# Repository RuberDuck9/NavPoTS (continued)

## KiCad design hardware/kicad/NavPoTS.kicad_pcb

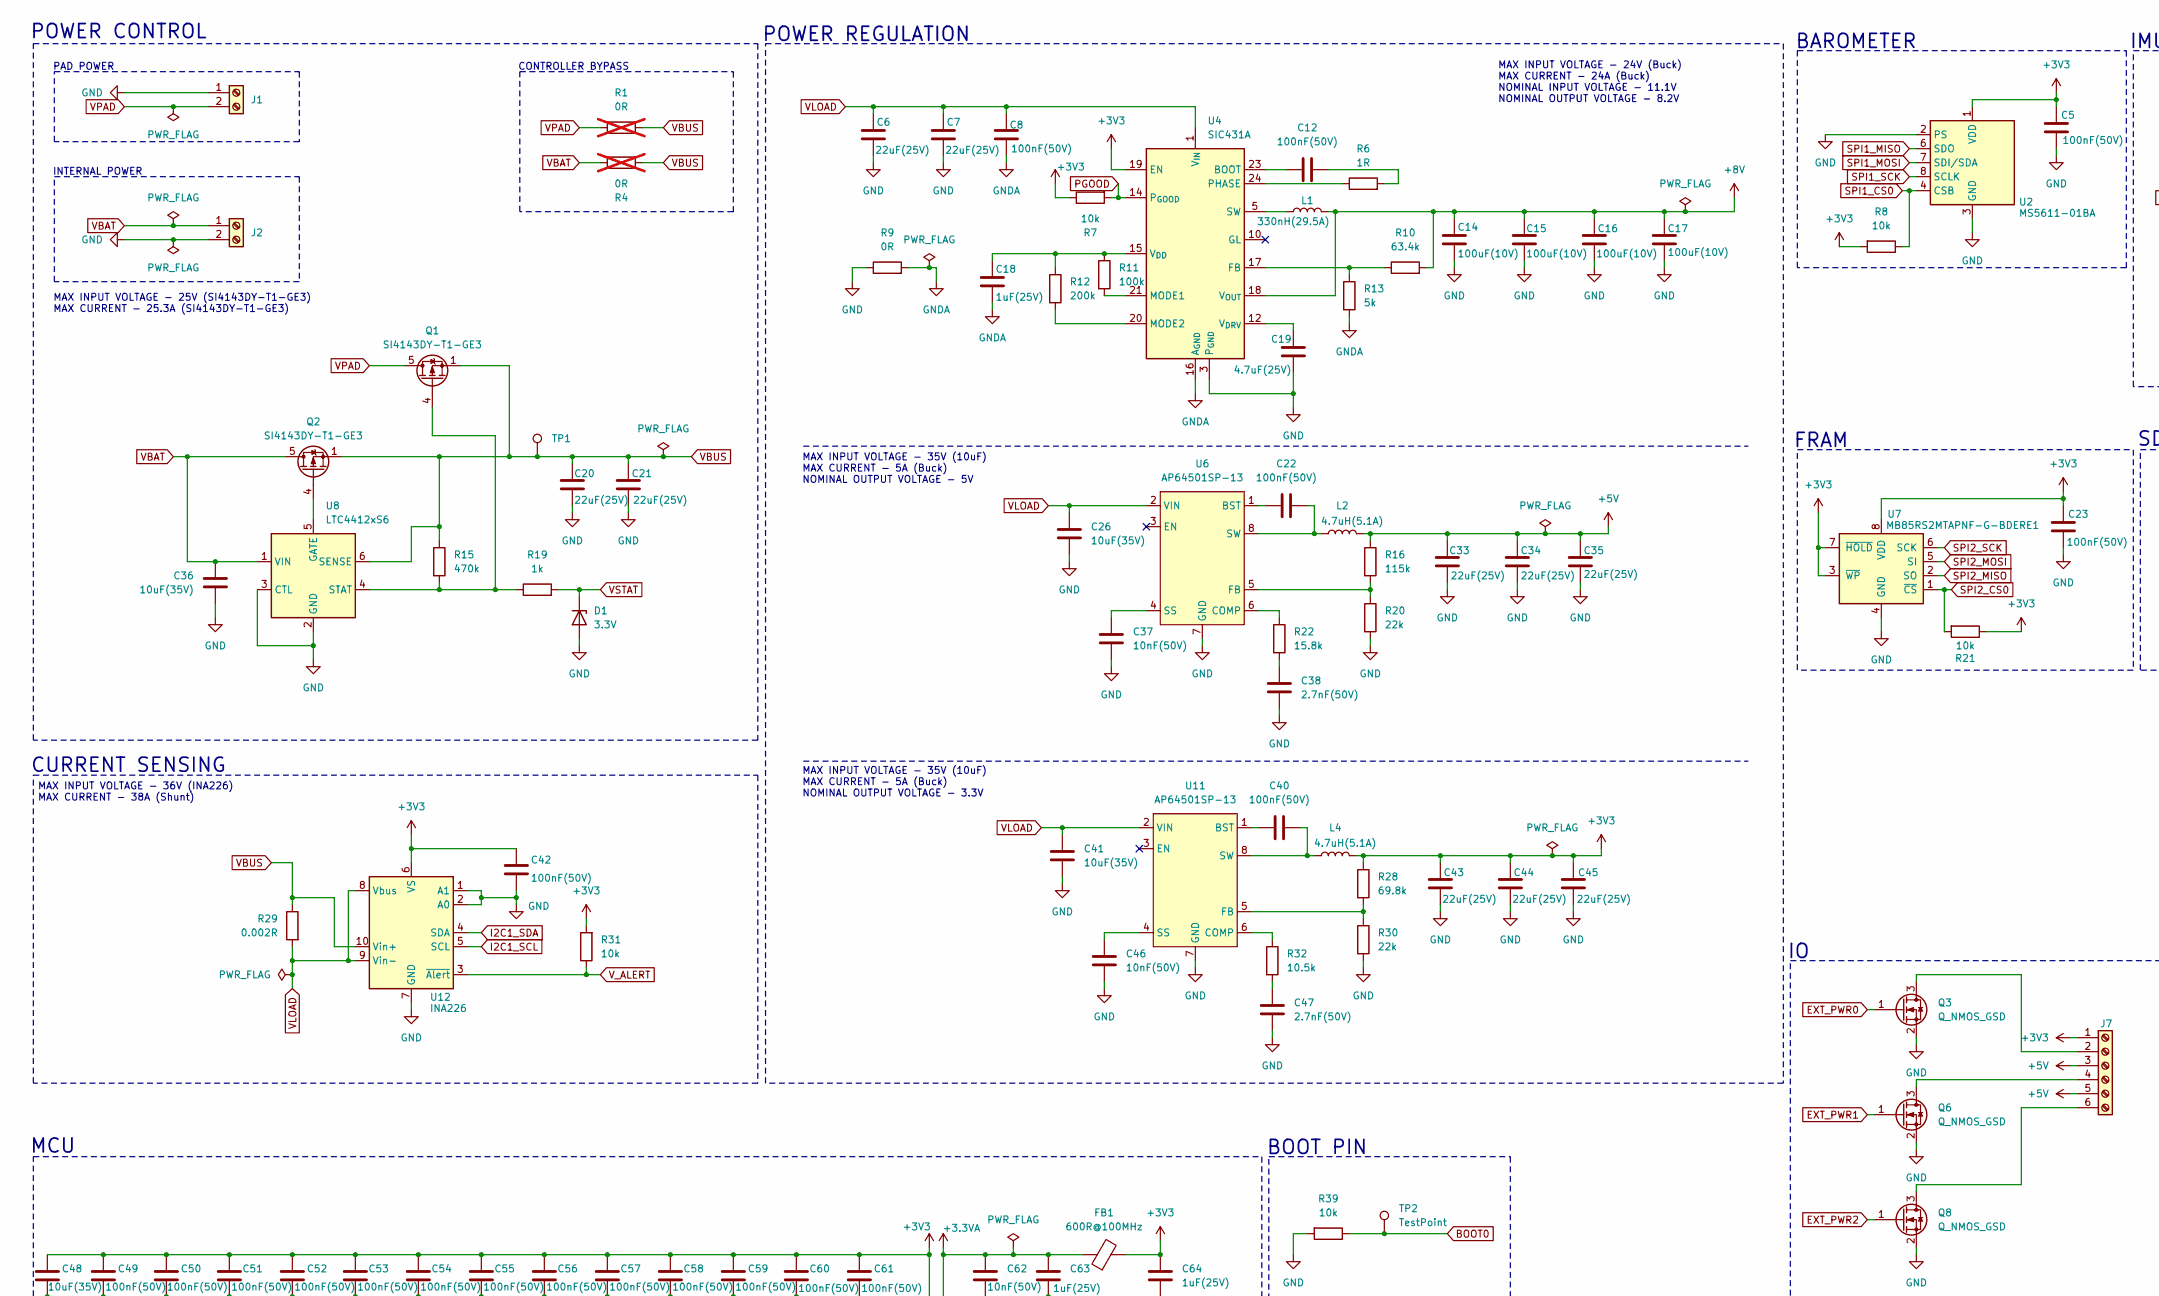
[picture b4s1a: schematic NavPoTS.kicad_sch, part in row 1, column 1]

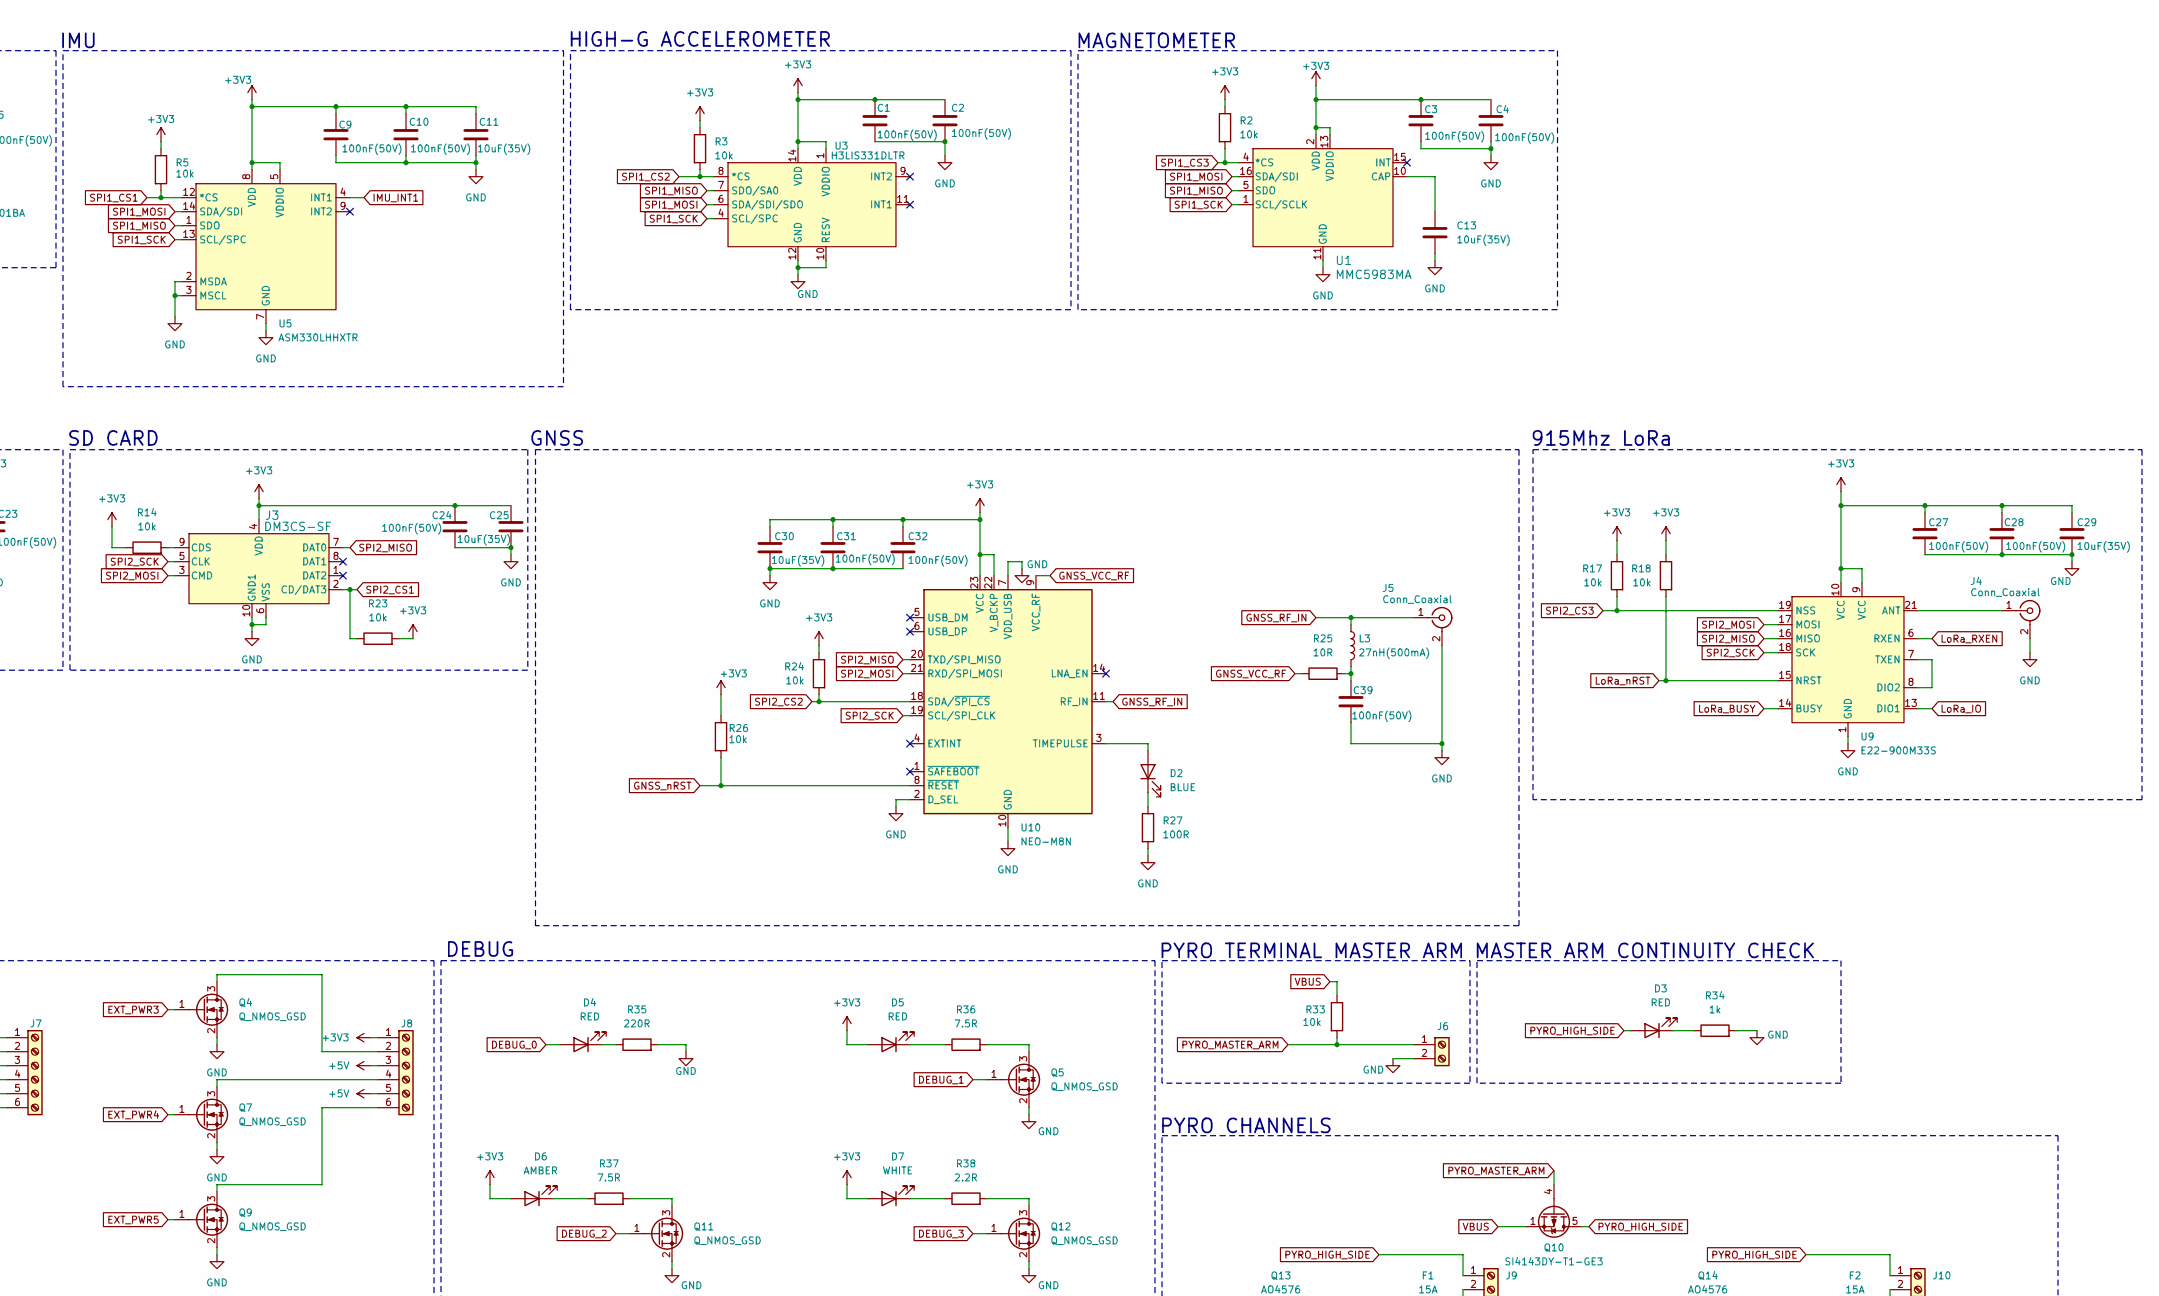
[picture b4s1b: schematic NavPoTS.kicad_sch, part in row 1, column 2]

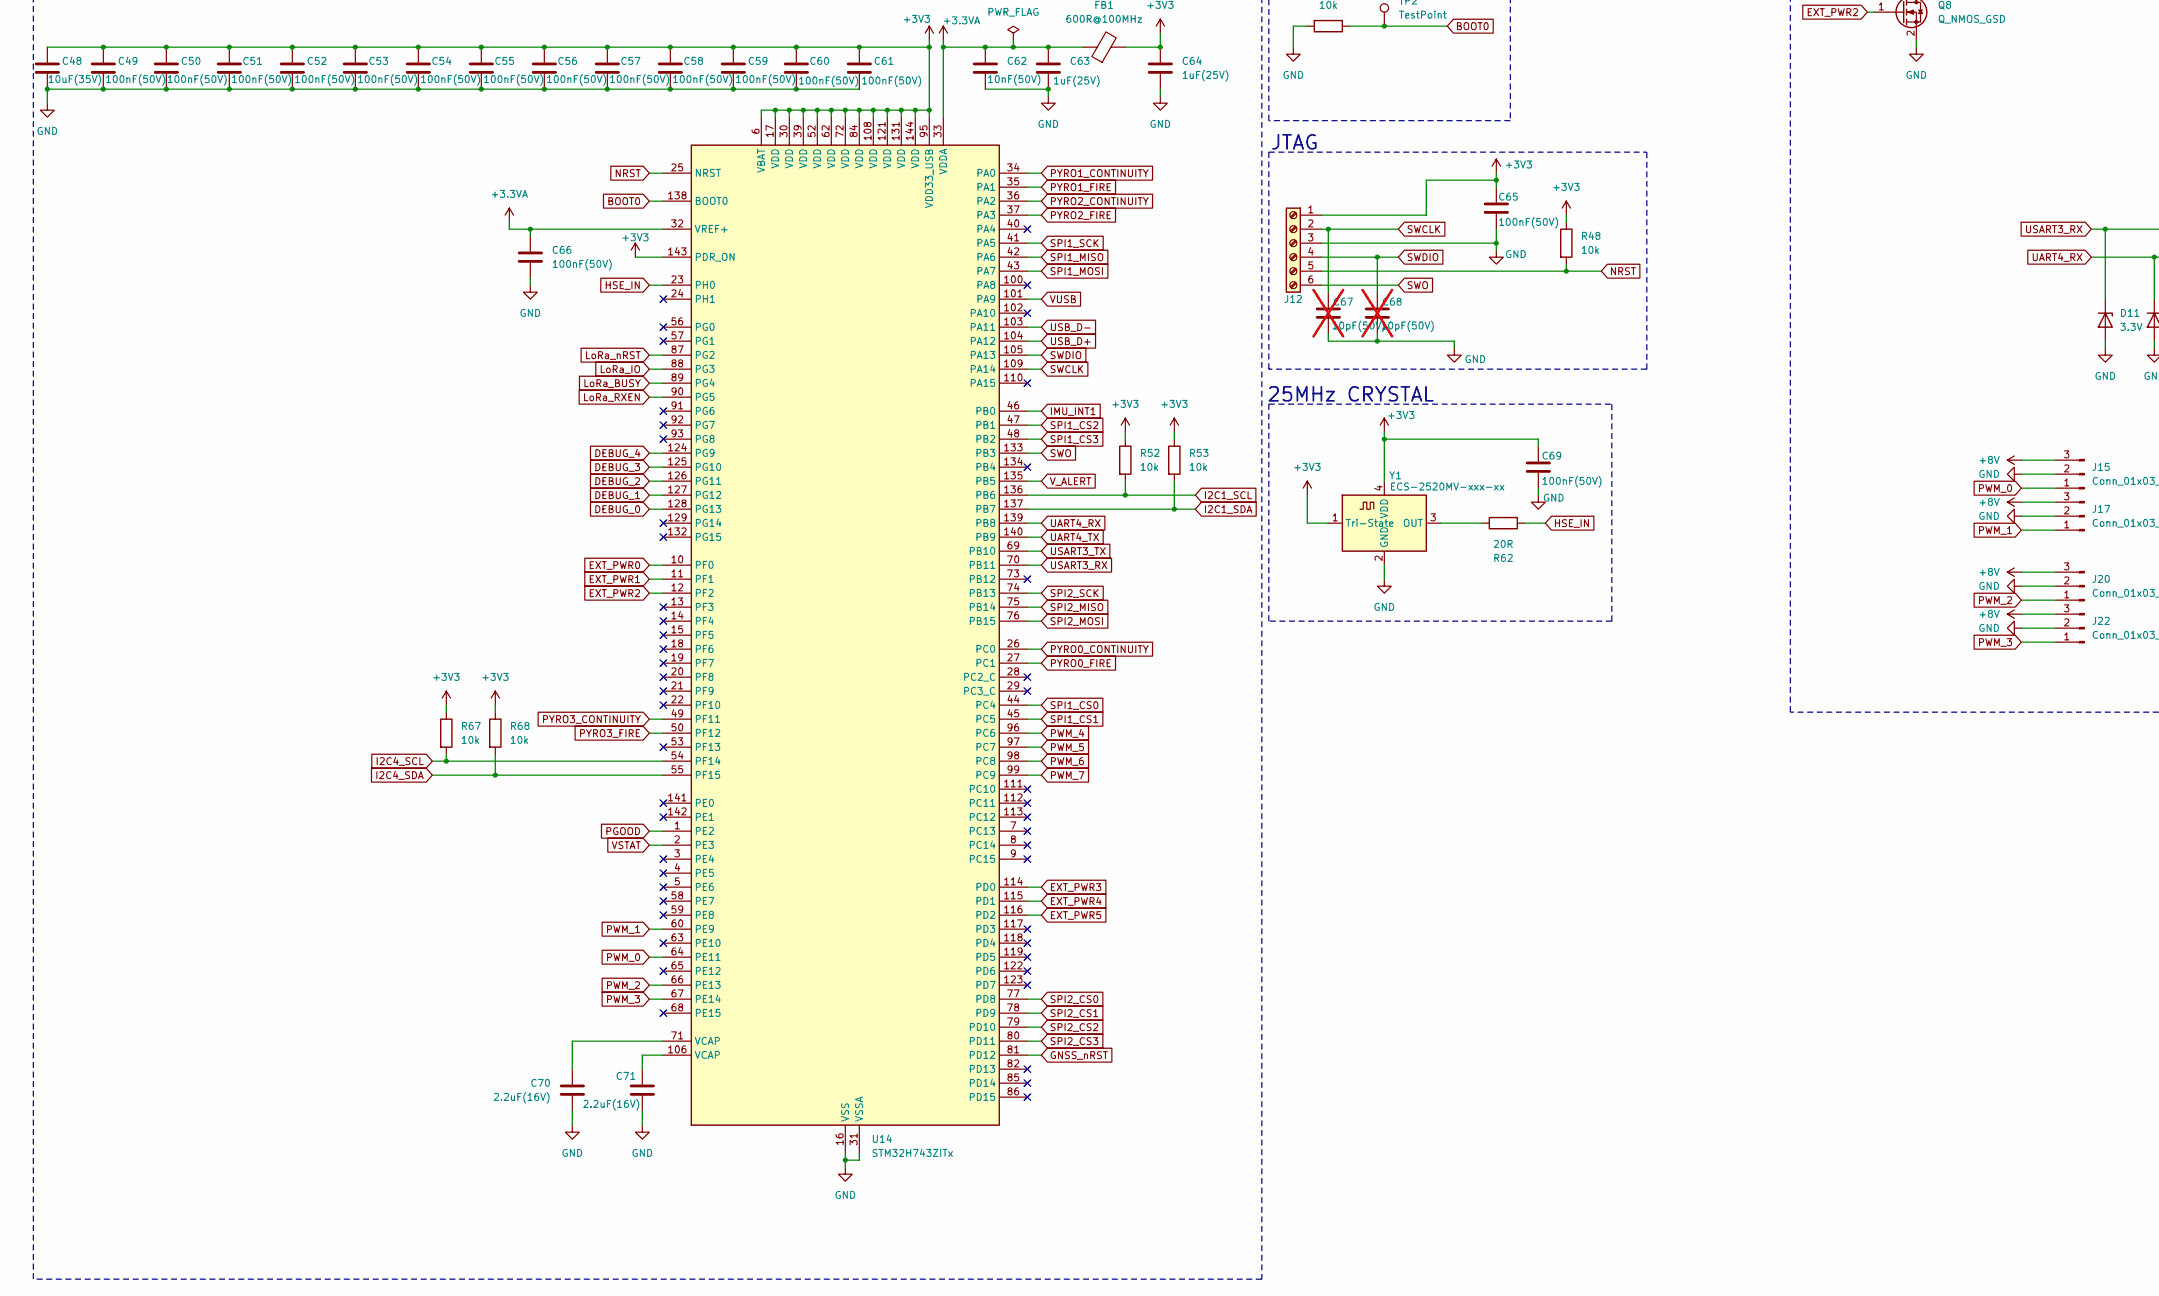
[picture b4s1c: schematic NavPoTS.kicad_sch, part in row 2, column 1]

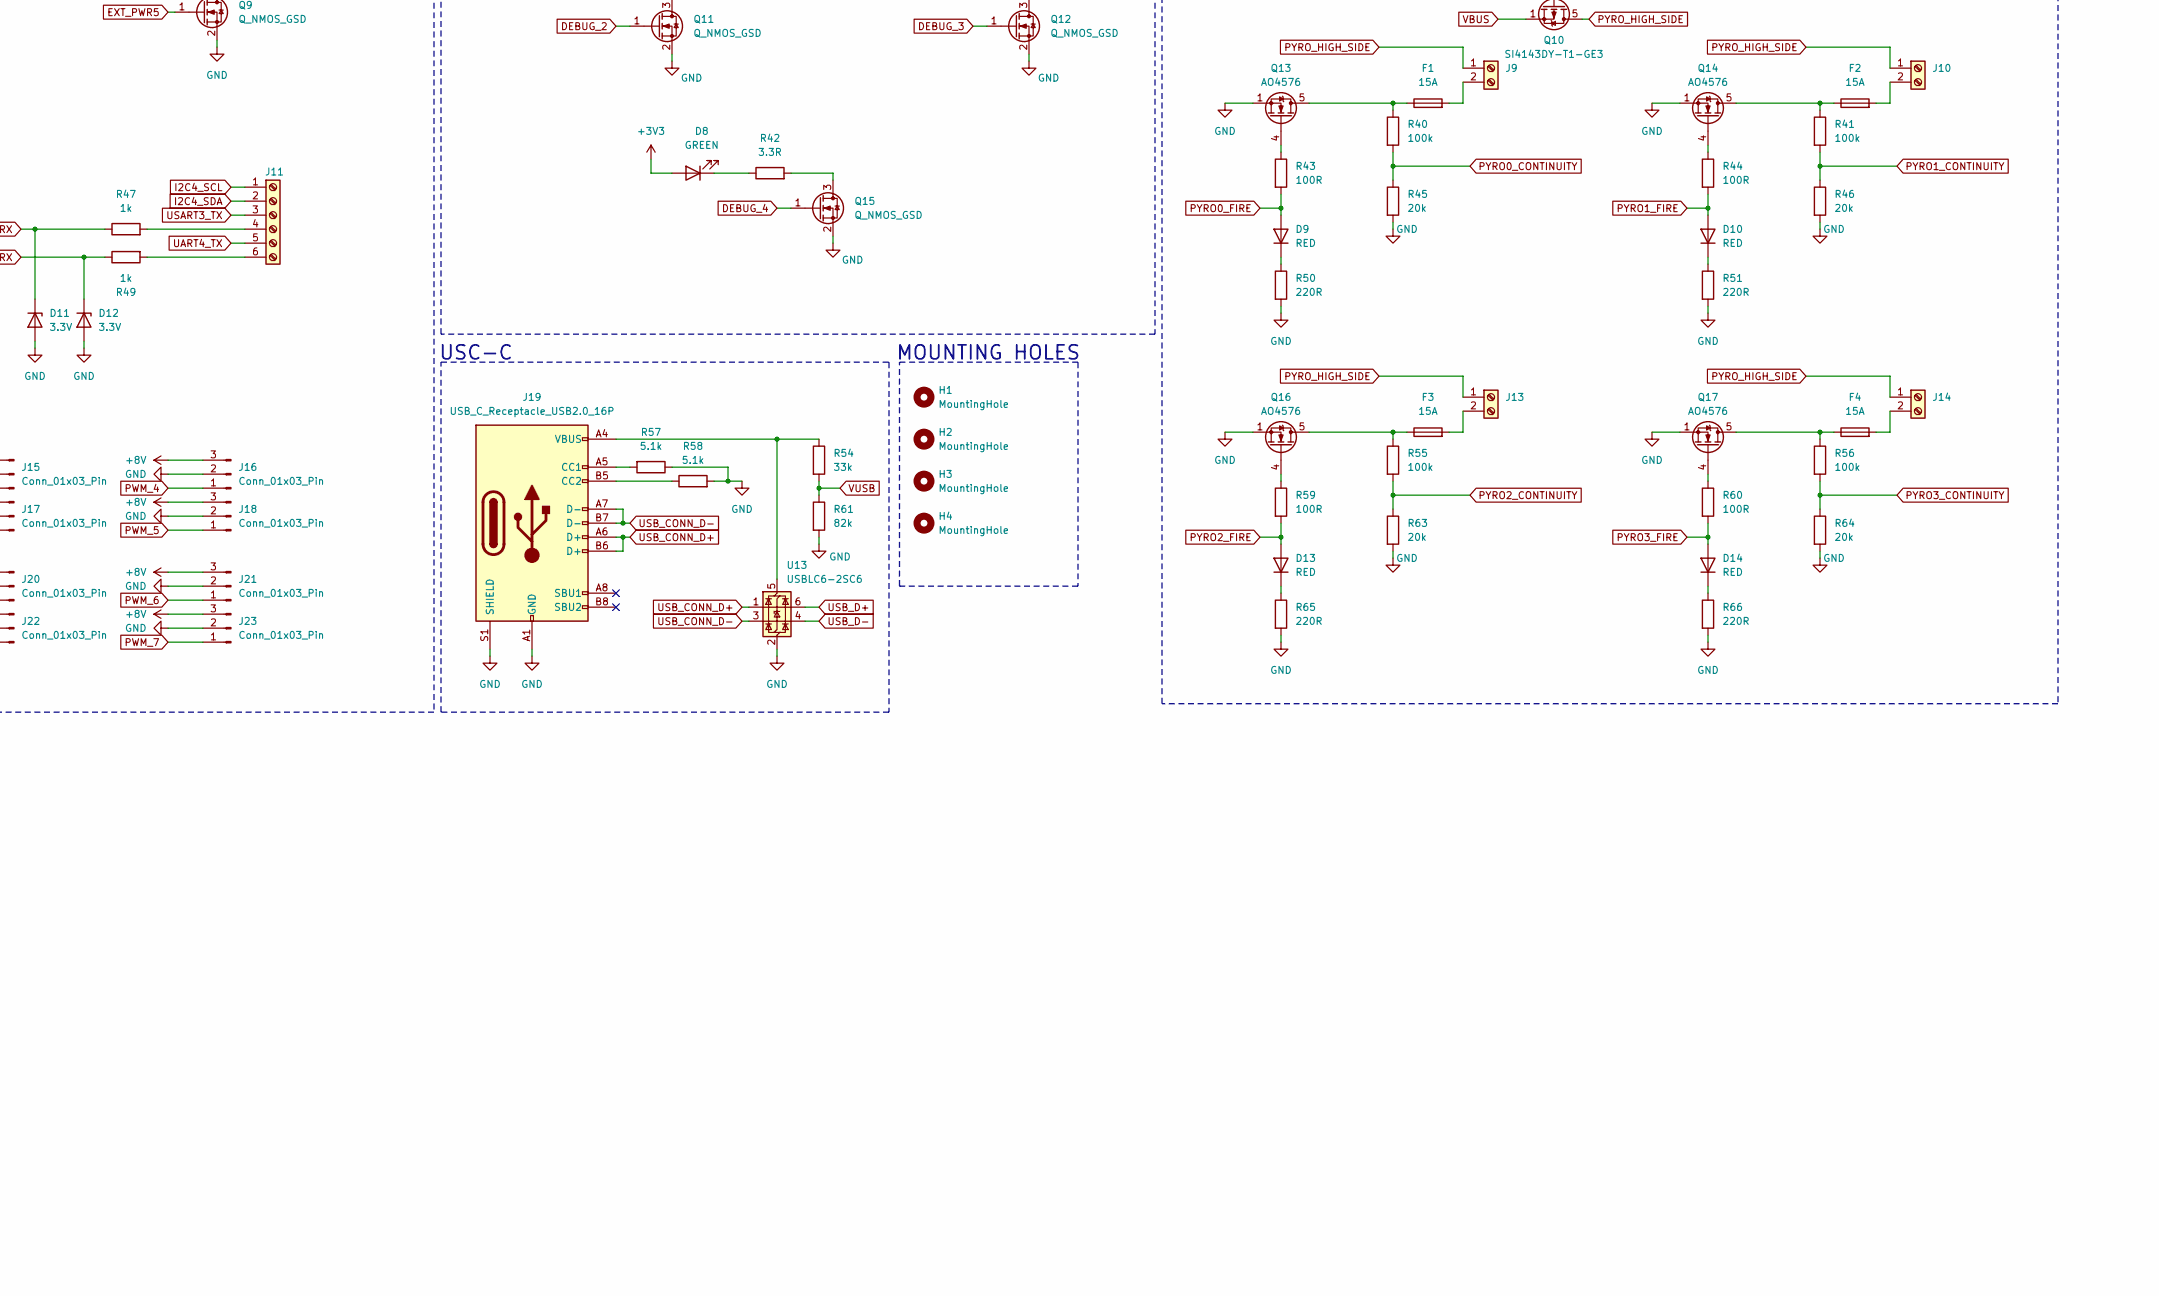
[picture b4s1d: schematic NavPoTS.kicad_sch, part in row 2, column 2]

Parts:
C1, C2, C3, C4, C5, C8, C9, C10, C12, C22, C23, C24, C27, C28, C31, C32, C39, C40, C42, C49, C50, C51, C52, C53, C54, C55, C56, C57, C58, C59, C60, C61, C65, C66, C69: 100nF(50V); C_0603_1608Metric_Pad1.08x0.95mm_HandSolder; MPN C0603C104K5RACTU
C6, C7, C20, C21, C33, C34, C35, C43, C44, C45: 22uF(25V); C_0805_2012Metric_Pad1.18x1.45mm_HandSolder; MPN GRM21BR61E226ME44L
C11, C13, C25, C26, C29, C30, C36, C41, C48: 10uF(35V); C_0603_1608Metric_Pad1.08x0.95mm_HandSolder; MPN GRM188R6YA106MA73D
C14, C15, C16, C17: 100uF(10V); C_1206_3216Metric_Pad1.33x1.80mm_HandSolder; MPN C3216X5R1A107M160AC
C18, C63, C64: 1uF(25V); C_0603_1608Metric_Pad1.08x0.95mm_HandSolder; MPN CL10B105KA8NNNC
C19: 4.7uF(25V); C_0603_1608Metric_Pad1.08x0.95mm_HandSolder; MPN GRM188R61E475KE11D
C37, C46, C62: 10nF(50V); C_0603_1608Metric_Pad1.08x0.95mm_HandSolder; MPN C0603C103K5RACTU
C38, C47: 2.7nF(50V); C_0603_1608Metric_Pad1.08x0.95mm_HandSolder; MPN GRM1885C1H272JA01D
C67, C68: 10pF(50V); C_0603_1608Metric_Pad1.08x0.95mm_HandSolder; MPN C0603C100J5GACTU; not fitted
C70, C71: 2.2uF(16V); C_0603_1608Metric_Pad1.08x0.95mm_HandSolder; MPN CL10A225KO8NNNC
D1, D11, D12: 3.3V; D_SOD-123; MPN MMSZ3V3T1G
D2: BLUE; LED_0603_1608Metric_Pad1.05x0.95mm_HandSolder; MPN LTST-C193TBKT-5A
D3, D4, D9, D10, D13, D14: RED; LED_0603_1608Metric_Pad1.05x0.95mm_HandSolder; MPN LTST-C190KRKT
D5: RED; LED_PLCC_2835_Handsoldering; MPN JE2835ARD-N-0001A0000-N0000001
D6: AMBER; LED_PLCC_2835_Handsoldering; MPN JE2835AAM-N-0001A0000-N0000001
D7: WHITE; LED_PLCC_2835_Handsoldering; MPN JE2835AWT-R-H40GA0000-N0000001
D8: GREEN; LED_PLCC_2835_Handsoldering; MPN JE2835AGR-N-0002A0000-N0000001
F1, F2, F3, F4: 15A; Fuse_1206_3216Metric_Pad1.42x1.75mm_HandSolder; MPN 0685H9150-01
FB1: 600R@100MHz; L_0805_2012Metric_Pad1.05x1.20mm_HandSolder; MPN HZ0805E601R-10
H1, H2, H3, H4: MountingHole; MountingHole_3.2mm_M3
J1, J2, J6, J9, J10, J13, J14: Screw_Terminal_01x02; CONN_ED555_2DS; MPN ED555/2DS
J3: DM3CS-SF; DM3CS-SF_HIR; MPN DM3CS-SF
J4, J5: Conn_Coaxial; COAX4GND_CONSMA001-C-G_TEC; MPN CONSMA001-C-G
J7, J8, J11, J12: Screw_Terminal_01x06; CONN_ED555_6DS; MPN ED555/6DS
J15, J16, J17, J18, J20, J21, J22, J23: Conn_01x03_Pin; PinHeader_1x03_P2.54mm_Vertical
J19: USB_C_Receptacle_USB2.0_16P; USB_C_Receptacle_GCT_USB4105-xx-A_16P_TopMnt_Horizontal; MPN USB4105-GF-A
L1: 330nH(29.5A); IND_IHLP-3232DZ_VIS; MPN IHLP3232DZERR33M01
L2, L4: 4.7uH(5.1A); L_Wuerth_MAPI-4030; MPN 74438357047
L3: 27nH(500mA); L_0603_1608Metric_Pad1.05x0.95mm_HandSolder; MPN LQG18HN27NJ00D
Q1, Q2, Q10: SI4143DY-T1-GE3; SOIC-8_3.9x4.9mm_P1.27mm; MPN SI4143DY-T1-GE3
Q3, Q4, Q6, Q7, Q8, Q9: Q_NMOS_GSD; SOT-23-3; MPN AO3400A
Q5, Q11, Q12, Q15: Q_NMOS_GSD; SOT-523; MPN DMG1012TQ-7
Q13, Q14, Q16, Q17: AO4576; SOIC-8_3.9x4.9mm_P1.27mm; MPN AO4576
R1, R4: 0R; R_0805_2012Metric_Pad1.20x1.40mm_HandSolder; MPN RC0805JR-070RL; not fitted
R2, R3, R5, R7, R8, R14, R17, R18, R21, R23, R24, R26, R31, R33, R39, R48, R52, R53, R67, R68: 10k; R_0603_1608Metric_Pad0.98x0.95mm_HandSolder; MPN RC0603FR-0710KL
R6: 1R; R_0603_1608Metric_Pad0.98x0.95mm_HandSolder; MPN RC0603FR-071RL
R9: 0R; R_0603_1608Metric_Pad0.98x0.95mm_HandSolder; MPN RC0603JR-070RL
R10: 63.4k; R_0603_1608Metric_Pad0.98x0.95mm_HandSolder; MPN RMCF0603FT63K4
R11, R40, R41, R55, R56: 100k; R_0603_1608Metric_Pad0.98x0.95mm_HandSolder; MPN RC0603FR-07100KL
R12: 200k; R_0603_1608Metric_Pad0.98x0.95mm_HandSolder; MPN RC0603FR-07200KL
R13: 5k; R_0603_1608Metric_Pad0.98x0.95mm_HandSolder; MPN RT0603BRE075KL
R15: 470k; R_0603_1608Metric_Pad0.98x0.95mm_HandSolder; MPN RMCF0603FT470K
R16: 115k; R_0603_1608Metric_Pad0.98x0.95mm_HandSolder; MPN RC0603FR-07115KL
R19, R34, R47, R49: 1k; R_0603_1608Metric_Pad0.98x0.95mm_HandSolder; MPN RC0603FR-071KL
R20, R30: 22k; R_0603_1608Metric_Pad0.98x0.95mm_HandSolder; MPN RC0603FR-0722KL
R22: 15.8k; R_0603_1608Metric_Pad0.98x0.95mm_HandSolder; MPN RC0603FR-0715K8L
R25: 10R; R_0603_1608Metric_Pad0.98x0.95mm_HandSolder; MPN RC0603FR-0710RL
R27, R43, R44, R59, R60: 100R; R_0603_1608Metric_Pad0.98x0.95mm_HandSolder; MPN RC0603FR-07100RL
R28: 69.8k; R_0603_1608Metric_Pad0.98x0.95mm_HandSolder; MPN RC0603FR-0769K8L
R29: 0.002R; R_2512_6332Metric_Pad1.40x3.35mm_HandSolder; MPN CRE2512-FZ-R002E-3
R32: 10.5k; R_0603_1608Metric_Pad0.98x0.95mm_HandSolder; MPN RC0603FR-0710K5L
R35, R50, R51, R65, R66: 220R; R_0603_1608Metric_Pad0.98x0.95mm_HandSolder; MPN RC0603FR-07220RL
R36, R37: 7.5R; R_0603_1608Metric_Pad0.98x0.95mm_HandSolder; MPN RC0603FR-077R5L
R38: 2.2R; R_0603_1608Metric_Pad0.98x0.95mm_HandSolder; MPN RC0603FR-072R2L
R42: 3.3R; R_0603_1608Metric_Pad0.98x0.95mm_HandSolder; MPN RC0603FR-073R3L
R45, R46, R63, R64: 20k; R_0603_1608Metric_Pad0.98x0.95mm_HandSolder; MPN RC0603FR-0720KL
R54: 33k; R_0603_1608Metric_Pad0.98x0.95mm_HandSolder; MPN RC0603FR-0733KL
R57, R58: 5.1k; R_0603_1608Metric_Pad0.98x0.95mm_HandSolder; MPN RC0603FR-075K1L
R61: 82k; R_0603_1608Metric_Pad0.98x0.95mm_HandSolder; MPN RC0603FR-0782KL
R62: 20R; R_0603_1608Metric_Pad0.98x0.95mm_HandSolder; MPN RC0603FR-0720RL
TP1, TP2: TestPoint; TestPoint_Pad_D1.5mm
U1: MMC5983MA; LGA-16_3x3mm_P0.5mm; MPN MMC5983MA
U2: MS5611-01BA; LGA-8_3x5mm_P1.25mm; MPN MS561101BA03-50
U3: H3LIS331DLTR; TFLGA16_3X3X1_STM-M; MPN H3LIS331DLTR
U4: SIC431A; Vishay_PowerPAK_MLP44-24L_ThermalVias; MPN SIC431AED-T1-GE3
U5: ASM330LHHXTR; LGA-14_3x2.5mm_P0.5mm_LayoutBorder3x4y; MPN ASM330LHHXTR
U6, U11: AP64501SP-13; Diodes_SO-8EP; MPN AP64501SP-13
U7: MB85RS2MTAPNF-G-BDERE1; SOIC-8_3.9x4.9mm_P1.27mm; MPN MB85RS2MTAPNF-G-BDERE1
U8: LTC4412xS6; TSOT-23-6; MPN LTC4412IS6#TRPBF
U9: E22-900M33S; MPN E22-900M33S
U10: NEO-M8N; ublox_NEO; MPN NEO-M8N-0
U12: INA226; VSSOP-10_3x3mm_P0.5mm; MPN INA226AIDGSR
U13: USBLC6-2SC6; SOT-23-6; MPN USBLC6-2SC6
U14: STM32H743ZITx; LQFP-144_20x20mm_P0.5mm; MPN STM32H743ZIT6
Y1: ECS-2520MV-xxx-xx; Oscillator_SMD_ECS_2520MV-xxx-xx-4Pin_2.5x2.0mm; MPN ECS-2520MV-250-CN-TR

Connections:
+3.3VA: C62.1, C63.1, C66.2, FB1.1, U14.32 (VREF+), U14.33 (VDDA)
+3V3: C1.1, C2.1, C3.1, C4.1, C5.1, C9.1, C10.1, C11.1, C23.1, C24.1, C25.1, C27.1, C28.1, C29.1, C30.1, C31.1, C32.1, C42.1, C43.1, C44.1, C45.1, C48.1, C49.1, C50.1, C51.1, C52.1, C53.1, C54.1, C55.1, C56.1, C57.1, C58.1, C59.1, C60.1, C61.1, C64.1, C65.1, C69.1, D5.2 (A), D6.2 (A), D7.2 (A), D8.2 (A), FB1.2, J3.4 (VDD), J7.1, J8.1, J12.1, L4.2, R2.1, R3.1, R5.1, R7.1, R8.2, R14.1, R17.1, R18.1, R21.1, R23.2, R24.1, R26.1, R28.1, R31.2, R48.1, R52.1, R53.1, R67.1, R68.1, U1.2 (VDD), U1.13 (VDDIO), U2.1 (VDD), U3.1 (VDDIO), U3.14 (VDD), U3.15 (RESV), U4.19 (EN), U5.5 (VDDIO), U5.8 (VDD), U7.3 (~WP), U7.7 (~HOLD), U7.8 (VDD), U9.9 (VCC), U9.10 (VCC), U10.22 (V_BCKP), U10.23 (VCC), U12.6 (VS), U14.6 (VBAT), U14.17 (VDD), U14.30 (VDD), U14.39 (VDD), U14.52 (VDD), U14.62 (VDD), U14.72 (VDD), U14.84 (VDD), U14.95 (VDD33_USB), U14.108 (VDD), U14.121 (VDD), U14.131 (VDD), U14.143 (PDR_ON), U14.144 (VDD), Y1.1 (Tri-State), Y1.4 (VDD)
+5V: C33.1, C34.1, C35.1, J7.3, J7.5, J8.3, J8.5, L2.2, R16.1
+8V: C14.1, C15.1, C16.1, C17.1, J15.3, J16.3, J17.3, J18.3, J20.3, J21.3, J22.3, J23.3, L1.2, R10.2, U4.18 (V_{OUT})
BOOT0: R39.1, TP2.1, U14.138 (BOOT0)
DEBUG_0: D4.2 (A), U14.128 (PG13)
DEBUG_1: Q5.1 (G), U14.127 (PG12)
DEBUG_2: Q11.1 (G), U14.126 (PG11)
DEBUG_3: Q12.1 (G), U14.125 (PG10)
DEBUG_4: Q15.1 (G), U14.124 (PG9)
EXT_PWR0: Q3.1 (G), U14.10 (PF0)
EXT_PWR1: Q6.1 (G), U14.11 (PF1)
EXT_PWR2: Q8.1 (G), U14.12 (PF2)
EXT_PWR3: Q4.1 (G), U14.114 (PD0)
EXT_PWR4: Q7.1 (G), U14.115 (PD1)
EXT_PWR5: Q9.1 (G), U14.116 (PD2)
GND: C1.2, C2.2, C3.2, C4.2, C5.2, C6.1, C7.2, C9.2, C10.2, C11.2, C13.2, C14.2, C15.2, C16.2, C17.2, C19.2, C20.1, C21.1, C23.2, C24.2, C25.2, C26.2, C27.2, C28.2, C29.2, C30.2, C31.2, C32.2, C33.2, C34.2, C35.2, C36.2, C37.1, C38.2, C39.2, C41.2, C42.2, C43.2, C44.2, C45.2, C46.1, C47.2, C48.2, C49.2, C50.2, C51.2, C52.2, C53.2, C54.2, C55.2, C56.2, C57.2, C58.2, C59.2, C60.2, C61.2, C62.2, C63.2, C64.2, C65.2, C66.1, C67.2, C68.2, C69.2, C70.1, C71.1, D1.2 (A), D11.2 (A), D12.2 (A), J1.1, J2.2, J3.6 (VSS), J3.10 (GND1), J3.11 (GND2), J3.12 (GND3), J3.13 (GND4), J4.2 (Ext), J5.2 (Ext), J6.2, J12.3, J15.2, J16.2, J17.2, J18.2, J19.A1 (GND), J19.A12 (GND), J19.B1 (GND), J19.B12 (GND), J19.S1 (SHIELD), J20.2, J21.2, J22.2, J23.2, Q3.2 (S), Q4.2 (S), Q5.2 (S), Q6.2 (S), Q7.2 (S), Q8.2 (S), Q9.2 (S), Q11.2 (S), Q12.2 (S), Q13.1, Q13.2, Q13.3, Q14.1, Q14.2, Q14.3, Q15.2 (S), Q16.1, Q16.2, Q16.3, Q17.1, Q17.2, Q17.3, R9.1, R20.2, R27.2, R30.2, R34.2, R35.2, R39.2, R45.2, R46.2, R50.2, R51.2, R57.1, R58.2, R61.2, R63.2, R64.2, R65.2, R66.2, U1.9 (GND), U1.11 (GND), U2.2 (PS), U2.3 (GND), U3.5 (GND), U3.10 (RESV), U3.12 (GND), U3.13 (GND), U3.16 (GND), U4.3 (P_{GND}), U4.4 (P_{GND}), U4.13 (P_{GND}), U4.27 (P_{GND}), U5.2 (MSDA), U5.3 (MSCL), U5.7 (GND), U6.7 (GND), U6.9 (GND), U7.4 (GND), U8.2 (GND), U8.3 (CTL), U9.1 (GND), U9.2 (GND), U9.3 (GND), U9.4 (GND), U9.5 (GND), U9.11 (GND), U9.12 (GND), U9.20 (GND), U9.22 (GND), U10.2 (D_SEL), U10.7 (VDD_USB), U10.10 (GND), U10.12 (GND), U10.13 (GND), U10.24 (GND), U11.7 (GND), U11.9 (GND), U12.1 (A1), U12.2 (A0), U12.7 (GND), U13.2 (GND), U14.16 (VSS), U14.31 (VSSA), U14.38 (VSS), U14.51 (VSS), U14.61 (VSS), U14.83 (VSS), U14.94 (VSS), U14.107 (VSS), U14.120 (VSS), U14.130 (VSS), Y1.2 (GND)
GNDA: C8.2, C18.2, R9.2, R13.2, U4.16 (A_{GND}), U4.25 (A_{GND})
GNSS_RF_IN: J5.1 (In), L3.1, U10.11 (RF_IN)
GNSS_VCC_RF: R25.1, U10.9 (VCC_RF)
GNSS_nRST: R26.2, U10.8 (~RESET), U14.81 (PD12)
HSE_IN: R62.2, U14.23 (PH0)
I2C1_SCL: R52.2, U12.5 (SCL), U14.136 (PB6)
I2C1_SDA: R53.2, U12.4 (SDA), U14.137 (PB7)
I2C4_SCL: J11.1, R67.2, U14.54 (PF14)
I2C4_SDA: J11.2, R68.2, U14.55 (PF15)
IMU_INT1: U5.4 (INT1), U14.46 (PB0)
LoRa_BUSY: U9.14 (BUSY), U14.89 (PG4)
LoRa_IO: U9.13 (DIO1), U14.88 (PG3)
LoRa_RXEN: U9.6 (RXEN), U14.90 (PG5)
LoRa_nRST: R18.2, U9.15 (NRST), U14.87 (PG2)
NRST: J12.5, R48.2, U14.25 (NRST)
unnamed: C12.2, R6.2
unnamed: C38.1, R22.2
unnamed: C39.1, L3.2, R25.2
unnamed: C47.1, R32.2
unnamed: C70.2, U14.71 (VCAP)
unnamed: C71.2, U14.106 (VCAP)
unnamed: D2.2 (A), U10.3 (TIMEPULSE)
unnamed: D2.1 (K), R27.1
unnamed: D3.1 (K), R34.1
unnamed: D4.1 (K), R35.1
unnamed: D5.1 (K), R36.1
unnamed: D6.1 (K), R37.1
unnamed: D7.1 (K), R38.1
unnamed: D8.1 (K), R42.1
unnamed: D9.1 (K), R50.1
unnamed: D10.1 (K), R51.1
unnamed: D13.1 (K), R65.1
unnamed: D14.1 (K), R66.1
unnamed: F1.1, Q13.5, Q13.6, Q13.7, Q13.8, R40.1
unnamed: F2.1, Q14.5, Q14.6, Q14.7, Q14.8, R41.1
unnamed: F3.1, Q16.5, Q16.6, Q16.7, Q16.8, R55.1
unnamed: F4.1, Q17.5, Q17.6, Q17.7, Q17.8, R56.1
unnamed: J3.9 (CDS), R14.2
unnamed: J4.1 (In), U9.21 (ANT)
unnamed: J7.2, Q3.3 (D)
unnamed: J7.4, Q6.3 (D)
unnamed: J7.6, Q8.3 (D)
unnamed: J8.2, Q4.3 (D)
unnamed: J8.4, Q7.3 (D)
unnamed: J8.6, Q9.3 (D)
unnamed: F1.2, J9.2
unnamed: F2.2, J10.2
unnamed: J11.4, R47.2
unnamed: J11.6, R49.2
unnamed: F3.2, J13.2
unnamed: F4.2, J14.2
unnamed: J19.A5 (CC1), R57.2
unnamed: J19.B5 (CC2), R58.1
unnamed: L1.1, U4.5 (SW), U4.6 (SW), U4.7 (SW), U4.8 (SW), U4.9 (SW)
unnamed: Q5.3 (D), R36.2
unnamed: Q11.3 (D), R37.2
unnamed: Q12.3 (D), R38.2
unnamed: Q13.4, R43.1
unnamed: Q14.4, R44.1
unnamed: Q15.3 (D), R42.2
unnamed: Q16.4, R59.1
unnamed: Q17.4, R60.1
unnamed: C13.1, U1.10 (CAP)
unnamed: C12.1, U4.23 (BOOT)
unnamed: R10.1, R13.1, U4.17 (FB)
unnamed: R11.2, U4.21 (MODE1)
unnamed: R12.2, U4.20 (MODE2)
unnamed: R6.1, U4.24 (PHASE)
unnamed: C18.1, R11.1, R12.1, U4.15 (V_{DD})
unnamed: C19.1, U4.12 (V_{DRV})
unnamed: C22.1, U6.1 (BST)
unnamed: R22.1, U6.6 (COMP)
unnamed: R16.2, R20.1, U6.5 (FB)
unnamed: C37.2, U6.4 (SS)
unnamed: C22.2, L2.1, U6.8 (SW)
unnamed: Q2.4, U8.5 (GATE)
unnamed: Q1.4, R15.2, R19.1, U8.4 (STAT)
unnamed: U9.7 (TXEN), U9.8 (DIO2)
unnamed: C40.1, U11.1 (BST)
unnamed: R32.1, U11.6 (COMP)
unnamed: R28.2, R30.1, U11.5 (FB)
unnamed: C46.2, U11.4 (SS)
unnamed: C40.2, L4.1, U11.8 (SW)
unnamed: J19.A4 (VBUS), J19.A9 (VBUS), J19.B4 (VBUS), J19.B9 (VBUS), R54.1, U13.5 (VBUS)
unnamed: R62.1, Y1.3 (OUT)
PGOOD: R7.2, U4.14 (P_{GOOD}), U14.1 (PE2)
PWM_0: J15.1, U14.64 (PE11)
PWM_1: J17.1, U14.60 (PE9)
PWM_2: J20.1, U14.66 (PE13)
PWM_3: J22.1, U14.67 (PE14)
PWM_4: J16.1, U14.96 (PC6)
PWM_5: J18.1, U14.97 (PC7)
PWM_6: J21.1, U14.98 (PC8)
PWM_7: J23.1, U14.99 (PC9)
PYRO0_CONTINUITY: R40.2, R45.1, U14.26 (PC0)
PYRO0_FIRE: D9.2 (A), R43.2, U14.27 (PC1)
PYRO1_CONTINUITY: R41.2, R46.1, U14.34 (PA0)
PYRO1_FIRE: D10.2 (A), R44.2, U14.35 (PA1)
PYRO2_CONTINUITY: R55.2, R63.1, U14.36 (PA2)
PYRO2_FIRE: D13.2 (A), R59.2, U14.37 (PA3)
PYRO3_CONTINUITY: R56.2, R64.1, U14.49 (PF11)
PYRO3_FIRE: D14.2 (A), R60.2, U14.50 (PF12)
PYRO_HIGH_SIDE: D3.2 (A), J9.1, J10.1, J13.1, J14.1, Q10.5, Q10.6, Q10.7, Q10.8
PYRO_MASTER_ARM: J6.1, Q10.4, R33.2
SPI1_CS0: R8.1, U2.4 (CSB), U2.5 (CSB), U14.44 (PC4)
SPI1_CS1: R5.2, U5.12 (*CS), U14.45 (PC5)
SPI1_CS2: R3.2, U3.8 (*CS), U14.47 (PB1)
SPI1_CS3: R2.2, U1.4 (*CS), U14.48 (PB2)
SPI1_MISO: U1.5 (SDO), U2.6 (SDO), U3.7 (SDO/SA0), U5.1 (SDO), U14.42 (PA6)
SPI1_MOSI: U1.16 (SDA/SDI), U2.7 (SDI/SDA), U3.6 (SDA/SDI/SDO), U5.14 (SDA/SDI), U14.43 (PA7)
SPI1_SCK: U1.1 (SCL/SCLK), U2.8 (SCLK), U3.4 (SCL/SPC), U5.13 (SCL/SPC), U14.41 (PA5)
SPI2_CS0: R21.2, U7.1 (~CS), U14.77 (PD8)
SPI2_CS1: J3.2 (CD/DAT3), R23.1, U14.78 (PD9)
SPI2_CS2: R24.2, U10.18 (SDA/~SPI_CS), U14.79 (PD10)
SPI2_CS3: R17.2, U9.19 (NSS), U14.80 (PD11)
SPI2_MISO: J3.7 (DAT0), U7.2 (SO), U9.16 (MISO), U10.20 (TXD/SPI_MISO), U14.75 (PB14)
SPI2_MOSI: J3.3 (CMD), U7.5 (SI), U9.17 (MOSI), U10.21 (RXD/SPI_MOSI), U14.76 (PB15)
SPI2_SCK: J3.5 (CLK), U7.6 (SCK), U9.18 (SCK), U10.19 (SCL/SPI_CLK), U14.74 (PB13)
SWCLK: C67.1, J12.2, U14.109 (PA14)
SWDIO: C68.1, J12.4, U14.105 (PA13)
SWO: J12.6, U14.133 (PB3)
UART4_RX: D12.1 (K), R49.1, U14.139 (PB8)
UART4_TX: J11.5, U14.140 (PB9)
USART3_RX: D11.1 (K), R47.1, U14.70 (PB11)
USART3_TX: J11.3, U14.69 (PB10)
USB_CONN_D+: J19.A6 (D+), J19.B6 (D+), U13.1 (I/O1)
USB_CONN_D-: J19.A7 (D-), J19.B7 (D-), U13.3 (I/O2)
USB_D+: U13.6 (I/O1), U14.104 (PA12)
USB_D-: U13.4 (I/O2), U14.103 (PA11)
VBAT: C36.1, J2.1, Q2.5, Q2.6, Q2.7, Q2.8, R4.1, U8.1 (VIN)
VBUS: C20.2, C21.2, Q1.1, Q1.2, Q1.3, Q2.1, Q2.2, Q2.3, Q10.1, Q10.2, Q10.3, R1.2, R4.2, R15.1, R29.1, R33.1, TP1.1, U8.6 (SENSE), U12.10 (Vin+)
VLOAD: C6.2, C7.1, C8.1, C26.1, C41.1, R29.2, U4.1 (V_{IN}), U4.2 (V_{IN}), U4.22 (V_{IN}), U4.26 (V_{IN}), U6.2 (VIN), U11.2 (VIN), U12.8 (Vbus), U12.9 (Vin-)
VPAD: J1.2, Q1.5, Q1.6, Q1.7, Q1.8, R1.1
VSTAT: D1.1 (K), R19.2, U14.2 (PE3)
VUSB: R54.2, R61.1, U14.101 (PA9)
V_ALERT: R31.1, U12.3 (~Alert), U14.135 (PB5)

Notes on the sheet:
915Mhz LoRa
PYRO CHANNELS
IMU
CURRENT SENSING
GNSS
PAD POWER
SD CARD
MAX INPUT VOLTAGE - 36V (INA226) MAX CURRENT - 38A (Shunt)
PYRO TERMINAL MASTER ARM
MAX INPUT VOLTAGE - 35V (10uF) MAX CURRENT - 5A (Buck) NOMINAL OUTPUT VOLTAGE - 3.3V
DEBUG
MCU
25MHz CRYSTAL
BOOT PIN
HIGH-G ACCELEROMETER
MOUNTING HOLES
MASTER ARM CONTINUITY CHECK
MAX INPUT VOLTAGE - 35V (10uF) MAX CURRENT - 5A (Buck) NOMINAL OUTPUT VOLTAGE - 5V
CONTROLLER BYPASS
POWER CONTROL
POWER REGULATION
JTAG
FRAM
BAROMETER
USC-C
MAGNETOMETER
MAX INPUT VOLTAGE - 24V (Buck) MAX CURRENT - 24A (Buck) NOMINAL INPUT VOLTAGE - 11.1V NOMINAL OUTPUT VOLTAGE - 8.2V
MAX INPUT VOLTAGE - 25V (SI4143DY-T1-GE3) MAX CURRENT - 25.3A (SI4143DY-T1-GE3)
INTERNAL POWER

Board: 4 copper layers, 223 parts (0 on the bottom side), 153 nets, no tracks yet.

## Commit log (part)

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2026-06-08 imported kicad library
2026-06-08 initial commit of NavPoTS schematic
2026-06-08 update libraries to include mpn and manufacturer
2026-06-09 sorted components into rough placement on pcb
2026-06-10 began work on splitting into 3 pcbs
2026-06-10 remaped pins and renamed pcb sections
2026-06-11 first draft of bridge pcb
2026-06-11 fixed solder mask issue with ffc connector
2026-06-12 first draft of south board layout and high current traces
2026-06-13 first draft of south board routing
2026-06-13 added gpio for future use on north and south boards
2026-06-14 finished first draft of north pcb routing
2026-06-14 v1.0
2026-06-25 update to kicad, begin cad work for pcb holder bracket
2026-06-25 remove fragment file from cad folder
